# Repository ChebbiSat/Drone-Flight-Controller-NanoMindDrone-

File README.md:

# Drone-Flight-Controller-NanoMindDrone-
This is an advanced PCB design for any homemade Drone.
The microcontroller is attached to several sesonrs and brushless motors controller to fly the drone from a radio controller.

Upwaork Contact:
Chebbi Thameur

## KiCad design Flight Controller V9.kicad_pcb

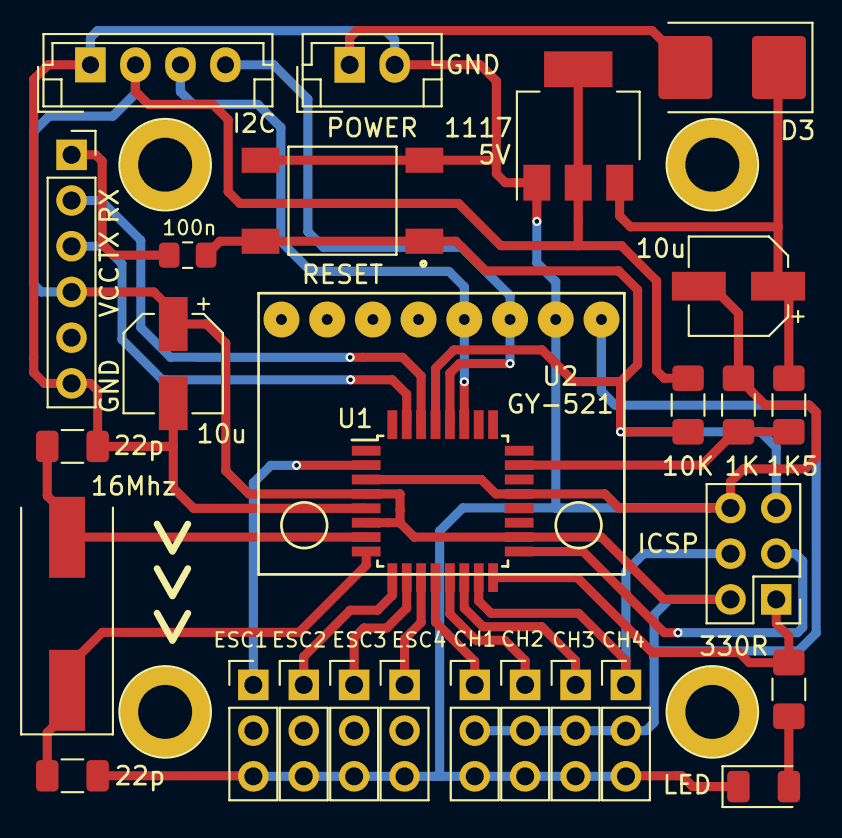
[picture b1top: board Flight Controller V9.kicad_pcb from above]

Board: 2 copper layers, 28 parts (0 on the bottom side), 24 nets.

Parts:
C1, C2: 22pF; C_1206_3216Metric
C4, C5: 10uF; CP_Elec_5x3.9
C6: 100nF; C_0805_2012Metric_Pad1.15x1.40mm_HandSolder
D2: LED_ALT; LED_1206_3216Metric
D3: D_Schottky; D_2816_7142Metric_Pad3.20x4.45mm_HandSolder
J1: Conn_01x02_Female; JST_EH_B02B-EH-A_1x02_P2.50mm_Vertical
J2: AVR-ISP-6; PinHeader_2x03_P2.54mm_Vertical
J3: Conn_01x04_Male; JST_EH_B04B-EH-A_1x04_P2.50mm_Vertical
J11, J12, J13, J14, J21, J22, J23, J24: Conn_01x03_Male; PinHeader_1x03_P2.54mm_Vertical
J25: Conn_01x06_Male; PinSocket_1x06_P2.54mm_Vertical
R1: 10K; R_1206_3216Metric_Pad1.42x1.75mm_HandSolder
R2: 330R; R_1206_3216Metric_Pad1.42x1.75mm_HandSolder
R5: 1K5; R_1206_3216Metric_Pad1.42x1.75mm_HandSolder
R6: 1K; R_1206_3216Metric_Pad1.42x1.75mm_HandSolder
S1: 2-1437565-7; SW_2-1437565-7
U1: ATmega328-AU; TQFP-32_7x7mm_P0.8mm
U2: GY-521
U4: LM1117-5.0; SOT-223-3_TabPin2
Y1: 16MHz; Crystal_SMD_HC49-SD

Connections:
A0: R5.2, R6.1, U1.23
D4: J11.1, U1.2
D5: J12.1, U1.9
D6: J13.1, U1.10
D7: J14.1, U1.11
D8: J21.1, U1.12
D9: J22.1, U1.13
D10: J23.1, U1.14
GND: C1.1, C2.1, C4.2, C5.2, D2.1, J1.2, J2.6, J3.1, J11.3, J12.3, J13.3, J14.3, J21.3, J22.3, J23.3, J24.3, J25.6, R6.2, S1.3, S1.4, U1.3, U1.5, U1.21, U2.2, U4.1
MISO: J2.1, R2.1, U1.16
MOSI: J2.4, J24.1, U1.15
unnamed: C4.1, D3.1, R5.1, U4.3
unnamed: C6.2, J25.1
unnamed: D2.2, R2.2
unnamed: D3.2, J1.1
OSC1: C1.2, U1.7, Y1.2
OSC2: C2.2, U1.8, Y1.1
RST: C6.1, J2.5, R1.1, S1.1, S1.2, U1.29
RX: J25.2, U1.30
SCK: J2.3, U1.17
SCL: J3.4, U1.28, U2.3
SDA: J3.3, U1.27, U2.4
TX: J25.3, U1.31
VBUS: C5.1, J2.2, J3.2, J21.2, J22.2, J23.2, J24.2, J25.4, R1.2, U1.4, U1.6, U1.18, U2.1, U4.2
